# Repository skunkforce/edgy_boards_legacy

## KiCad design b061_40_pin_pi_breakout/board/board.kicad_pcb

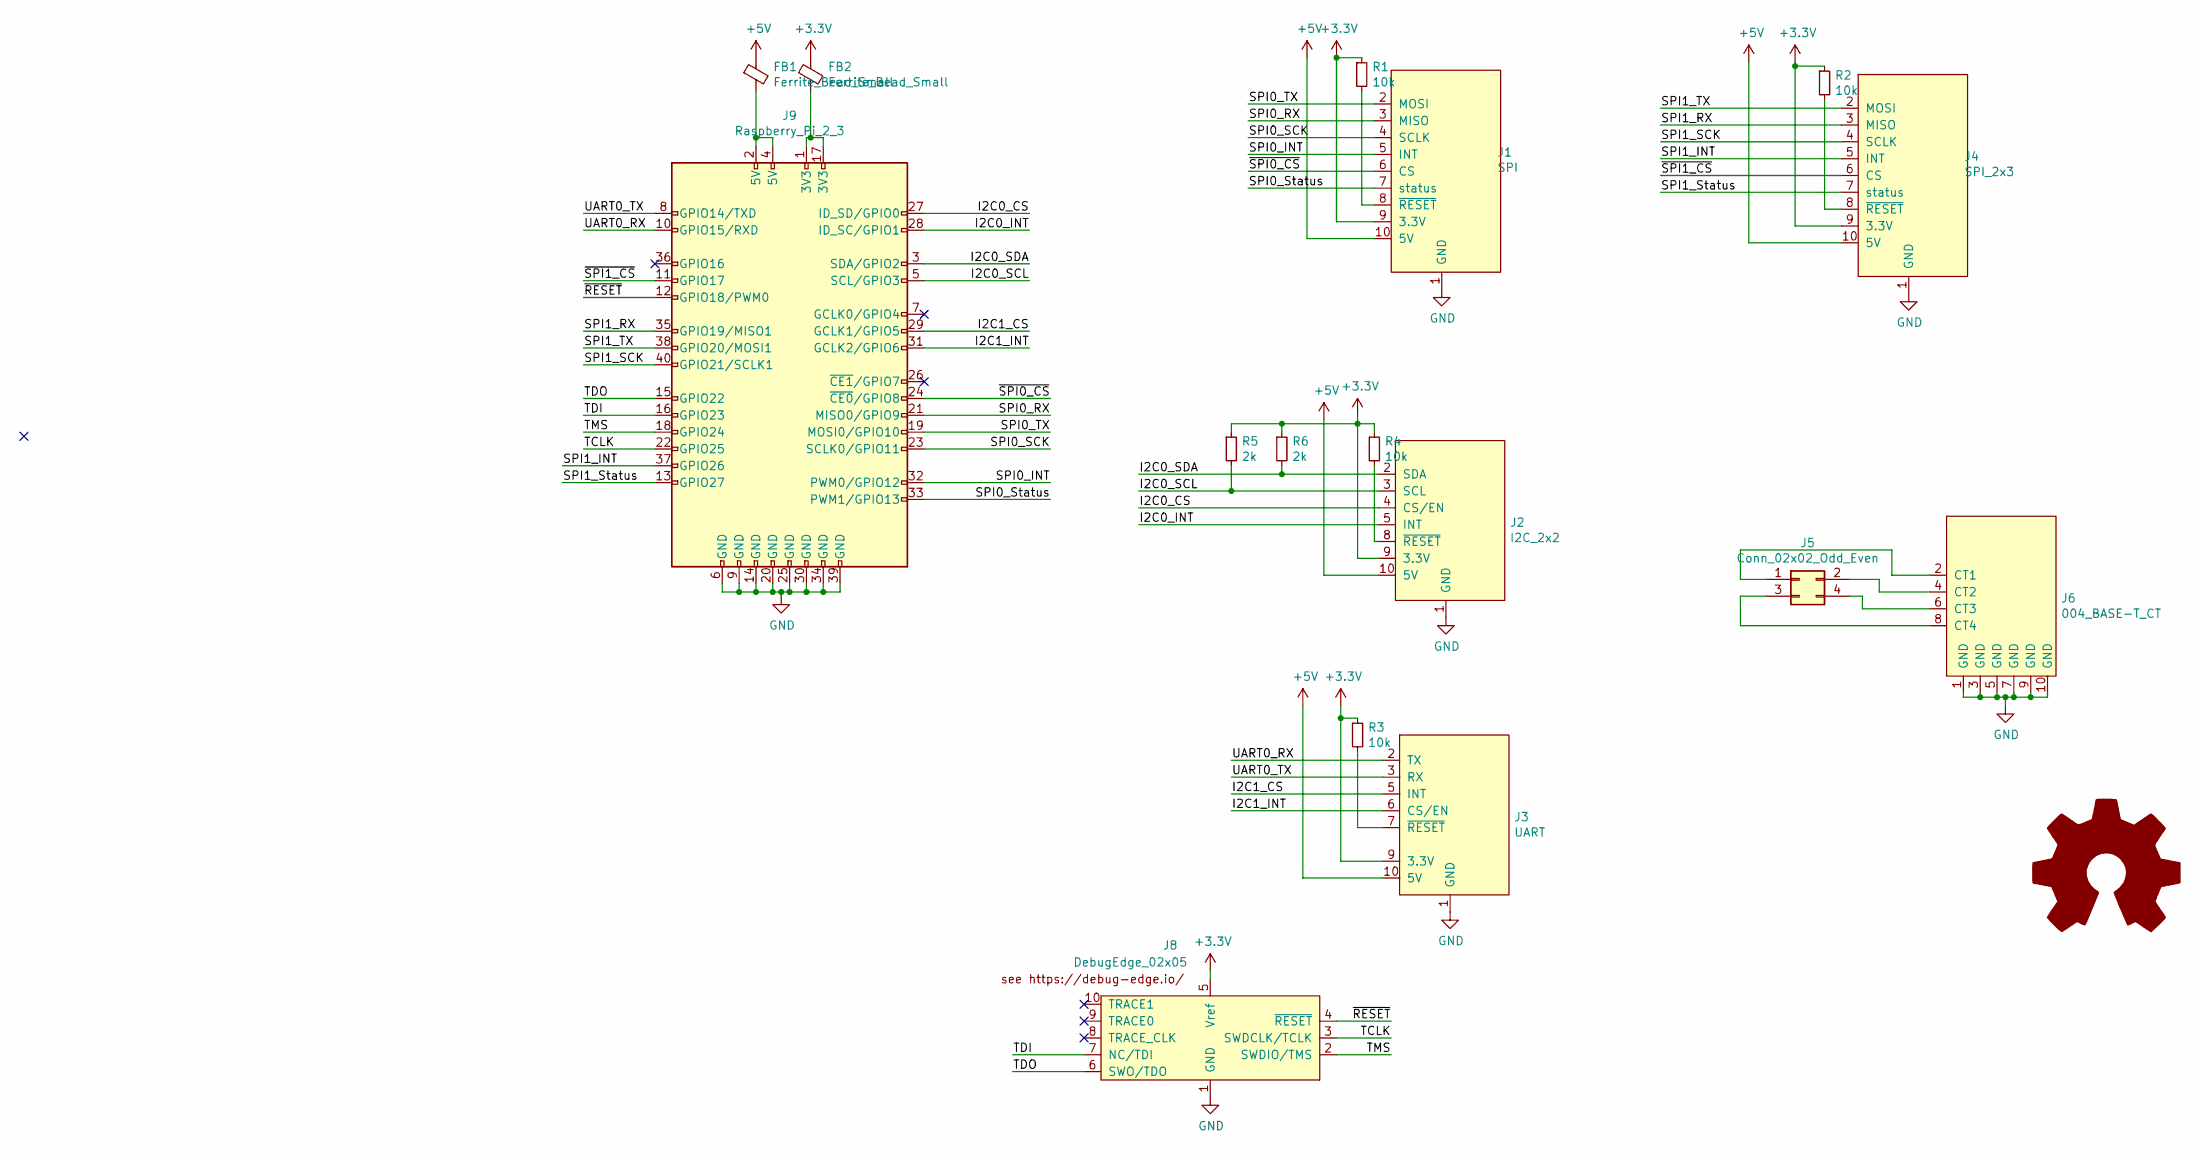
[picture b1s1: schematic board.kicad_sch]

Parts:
FB1, FB2: Ferrite_Bead_Small; L_0805_2012Metric
J1: SPI; on_edge_2x05_up_host
J2: I2C_2x2; on_edge_2x05_host
J3: UART; on_edge_2x05_host
J4: SPI_2x3; on_edge_2x05_host
J5: Conn_02x02_Odd_Even; PinSocket_2x02_P2.54mm_Vertical
J6: 004_BASE-T_CT; on_edge_2x05_up_host
J8: DebugEdge_02x05; debug_edge_2x05_host
J9: Raspberry_Pi_2_3; PinSocket_2x20_P2.54mm_Vertical
R1, R2, R3, R4: 10k; R_0603_1608Metric
R5, R6: 2k; R_0603_1608Metric
l1: Logo_Open_Hardware_Large; OSHW-Logo2_7.3x6mm_SilkScreen

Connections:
+3V3: FB2.1, J1.9 (3.3V), J2.9 (3.3V), J3.9 (3.3V), J4.9 (3.3V), J8.5 (Vref), R1.1, R2.1, R3.1, R4.1, R5.1, R6.1
+5V: FB1.1, J1.10 (5V), J2.10 (5V), J3.10 (5V), J4.10 (5V)
/I2C0_CS: J2.4 (CS/EN), J9.27 (ID_SD/GPIO0)
/I2C0_INT: J2.5 (INT), J9.28 (ID_SC/GPIO1)
/I2C0_SCL: J2.3 (SCL), J9.5 (SCL/GPIO3), R5.2
/I2C0_SDA: J2.2 (SDA), J9.3 (SDA/GPIO2), R6.2
/I2C1_CS: J3.5 (INT), J9.29 (GCLK1/GPIO5)
/I2C1_INT: J3.6 (CS/EN), J9.31 (GCLK2/GPIO6)
/SPI0_INT: J1.5 (INT), J9.32 (PWM0/GPIO12)
/SPI0_RX: J1.3 (MISO), J9.21 (MISO0/GPIO9)
/SPI0_SCK: J1.4 (SCLK), J9.23 (SCLK0/GPIO11)
/SPI0_Status: J1.7 (status), J9.33 (PWM1/GPIO13)
/SPI0_TX: J1.2 (MOSI), J9.19 (MOSI0/GPIO10)
/SPI1_INT: J4.5 (INT), J9.37 (GPIO26)
/SPI1_RX: J4.3 (MISO), J9.35 (GPIO19/MISO1)
/SPI1_SCK: J4.4 (SCLK), J9.40 (GPIO21/SCLK1)
/SPI1_Status: J4.7 (status), J9.13 (GPIO27)
/SPI1_TX: J4.2 (MOSI), J9.38 (GPIO20/MOSI1)
/TCLK: J8.3 (SWDCLK/TCLK), J9.22 (GPIO25)
/TDI: J8.7 (NC/TDI), J9.16 (GPIO23)
/TDO: J8.6 (SWO/TDO), J9.15 (GPIO22)
/TMS: J8.2 (SWDIO/TMS), J9.18 (GPIO24)
/UART0_RX: J3.2 (TX), J9.10 (GPIO15/RXD)
/UART0_TX: J3.3 (RX), J9.8 (GPIO14/TXD)
/~RESET: J8.4 (~RESET), J9.12 (GPIO18/PWM0)
/~SPI0_CS: J1.6 (CS), J9.24 (~CE0/GPIO8)
/~SPI1_CS: J4.6 (CS), J9.11 (GPIO17)
GND: J1.1 (GND), J2.1 (GND), J3.1 (GND), J4.1 (GND), J6.1 (GND), J6.3 (GND), J6.5 (GND), J6.7 (GND), J6.9 (GND), J6.10 (GND), J8.1 (GND), J9.6 (GND), J9.9 (GND), J9.14 (GND), J9.20 (GND), J9.25 (GND), J9.30 (GND), J9.34 (GND), J9.39 (GND)
unnamed: FB1.2, J9.2 (5V), J9.4 (5V)
unnamed: FB2.2, J9.1 (3V3), J9.17 (3V3)
unnamed: J1.8 (~RESET), R1.2
unnamed: J2.8 (~RESET), R4.2
unnamed: J3.7 (~RESET), R3.2
unnamed: J4.8 (~RESET), R2.2
unnamed: J5.1, J6.2 (CT1)
unnamed: J5.2, J6.4 (CT2)
unnamed: J5.3, J6.8 (CT4)
unnamed: J5.4, J6.6 (CT3)

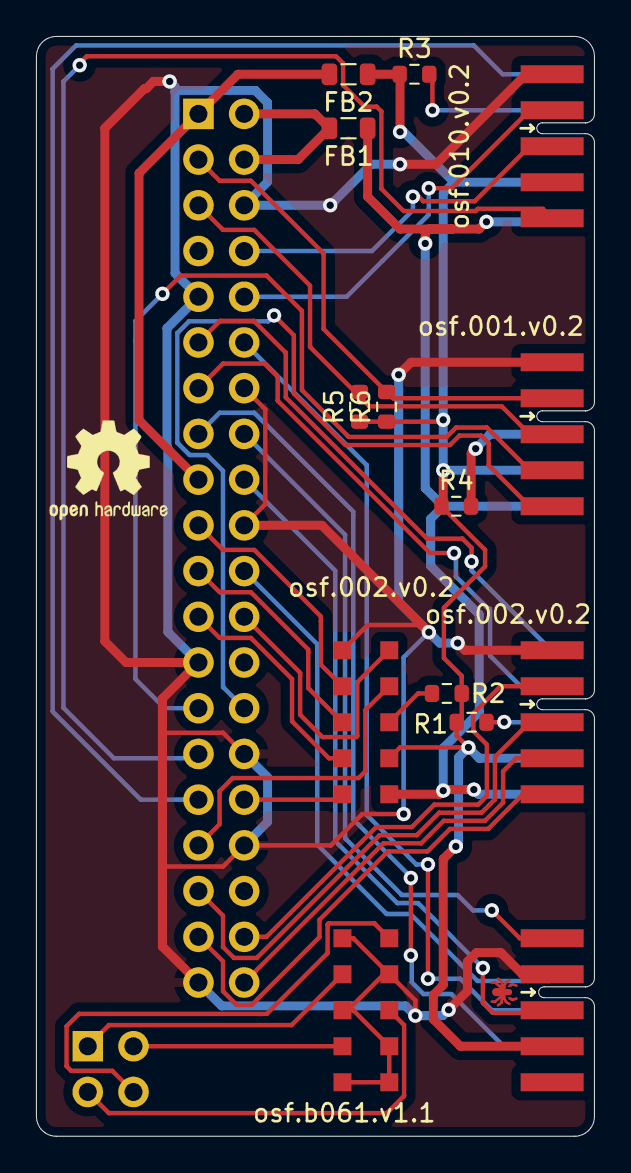
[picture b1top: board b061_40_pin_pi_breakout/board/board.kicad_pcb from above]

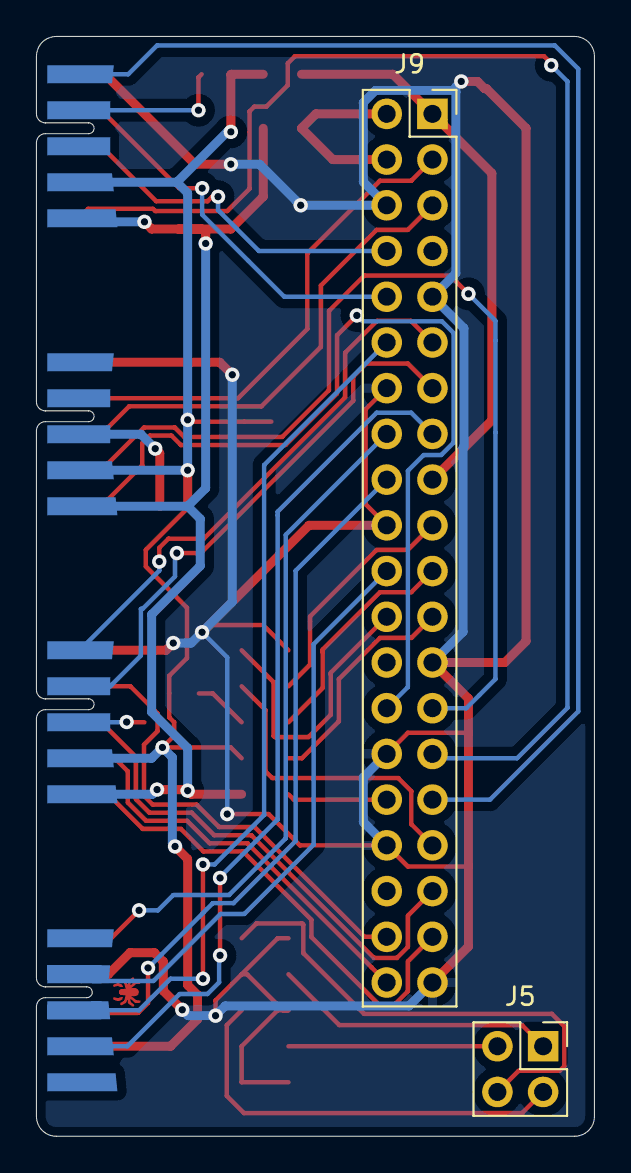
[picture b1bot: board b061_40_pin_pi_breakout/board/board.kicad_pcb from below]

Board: 2 copper layers, 31.0 x 61.1 mm, 17 parts (2 on the bottom side), 38 nets.

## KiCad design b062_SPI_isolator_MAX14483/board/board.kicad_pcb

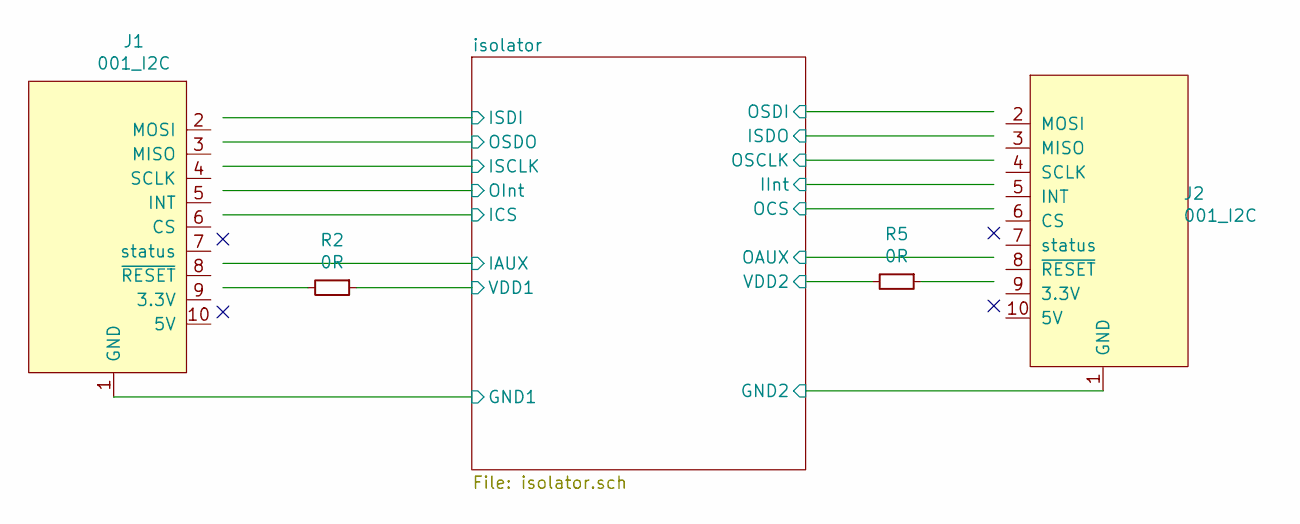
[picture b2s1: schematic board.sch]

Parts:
J1: 001_I2C; on_edge_2x05_device
J2: 001_I2C; on_edge_2x05_host
R2, R5: 0R; R_0603_1608Metric

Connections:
/isolator/GND1: J1.1 (GND); also elsewhere on the board
/isolator/GND2: J2.1 (GND); also elsewhere on the board
/isolator/IAUX: J1.8 (~RESET); also elsewhere on the board
/isolator/ICS: J1.6 (CS); also elsewhere on the board
/isolator/IInt: J2.5 (INT); also elsewhere on the board
/isolator/ISCLK: J1.4 (SCLK); also elsewhere on the board
/isolator/ISDI: J1.2 (MOSI); also elsewhere on the board
/isolator/ISDO: J2.3 (MISO); also elsewhere on the board
/isolator/OAUX: J2.8 (~RESET); also elsewhere on the board
/isolator/OCS: J2.6 (CS); also elsewhere on the board
/isolator/OInt: J1.5 (INT); also elsewhere on the board
/isolator/OSCLK: J2.4 (SCLK); also elsewhere on the board
/isolator/OSDI: J2.2 (MOSI); also elsewhere on the board
/isolator/OSDO: J1.3 (MISO); also elsewhere on the board
/isolator/VDD1: R2.1; also elsewhere on the board
/isolator/VDD2: R5.2; also elsewhere on the board
unnamed: J1.9 (3.3V), R2.2
unnamed: J2.9 (3.3V), R5.1

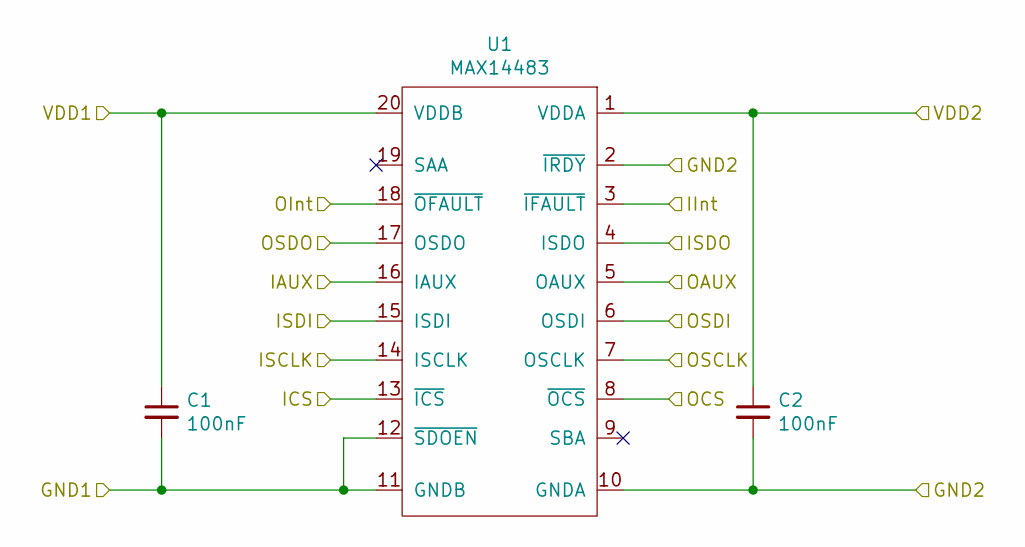
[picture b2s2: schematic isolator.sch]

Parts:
C1, C2: 100nF; C_0603_1608Metric
U1: MAX14483; SSOP-20_5.3x7.2mm_P0.65mm

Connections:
/isolator/GND1: C1.2, U1.11 (GNDB), U1.12 (~SDOEN); also elsewhere on the board
/isolator/GND2: C2.2, U1.2 (~IRDY), U1.10 (GNDA); also elsewhere on the board
/isolator/IAUX: U1.16 (IAUX); also elsewhere on the board
/isolator/ICS: U1.13 (~ICS); also elsewhere on the board
/isolator/IInt: U1.3 (~IFAULT); also elsewhere on the board
/isolator/ISCLK: U1.14 (ISCLK); also elsewhere on the board
/isolator/ISDI: U1.15 (ISDI); also elsewhere on the board
/isolator/ISDO: U1.4 (ISDO); also elsewhere on the board
/isolator/OAUX: U1.5 (OAUX); also elsewhere on the board
/isolator/OCS: U1.8 (~OCS); also elsewhere on the board
/isolator/OInt: U1.18 (~OFAULT); also elsewhere on the board
/isolator/OSCLK: U1.7 (OSCLK); also elsewhere on the board
/isolator/OSDI: U1.6 (OSDI); also elsewhere on the board
/isolator/OSDO: U1.17 (OSDO); also elsewhere on the board
/isolator/VDD1: C1.1, U1.20 (VDDB); also elsewhere on the board
/isolator/VDD2: C2.1, U1.1 (VDDA); also elsewhere on the board

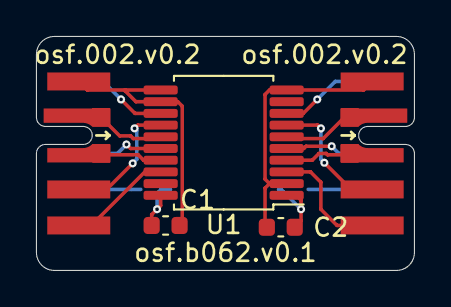
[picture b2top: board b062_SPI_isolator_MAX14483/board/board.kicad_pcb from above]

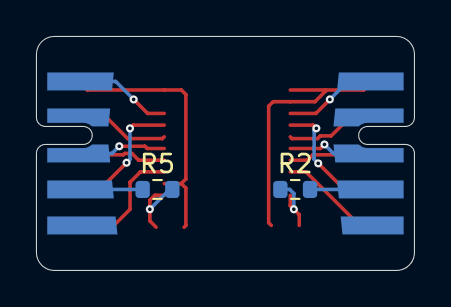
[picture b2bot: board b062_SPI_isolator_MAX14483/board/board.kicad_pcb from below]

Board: 2 copper layers, 21.0 x 13.0 mm, 7 parts (2 on the bottom side), 18 nets.

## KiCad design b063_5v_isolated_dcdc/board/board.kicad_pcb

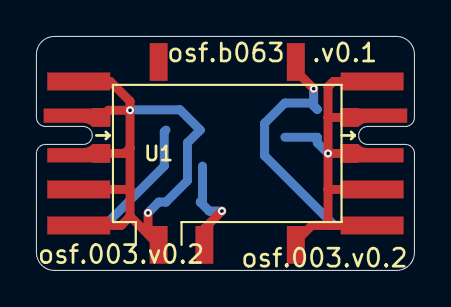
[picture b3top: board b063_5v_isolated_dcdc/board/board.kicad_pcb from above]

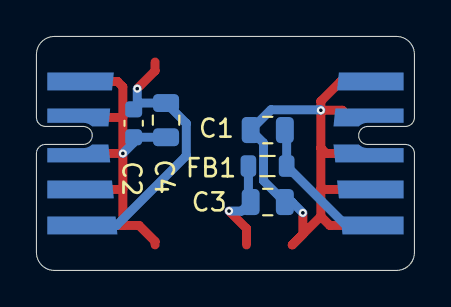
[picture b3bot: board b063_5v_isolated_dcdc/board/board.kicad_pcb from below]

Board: 2 copper layers, 21.0 x 13.0 mm, 8 parts (5 on the bottom side), 5 nets.

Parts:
C1, C3, C4: 10uF; C_0805_2012Metric
C2: 100nF; C_0603_1608Metric
FB1: 0R; L_0805_2012Metric
J1: 003_power; on_edge_2x05_device
J2: 003_power; on_edge_2x05_host
U1: PDS2-S5

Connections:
/isolator/GND1: C1.2, C3.2, J1.1, J1.2, J1.3, J1.4, J1.5, U1.1
/isolator/GND2: C2.2, C4.2, J2.1, J2.2, J2.3, J2.4, J2.5, U1.4
/isolator/VDD1: C1.1, FB1.2, J1.10
/isolator/VDD2: C2.1, C4.1, J2.10, U1.5
unnamed: C3.1, FB1.1, U1.2

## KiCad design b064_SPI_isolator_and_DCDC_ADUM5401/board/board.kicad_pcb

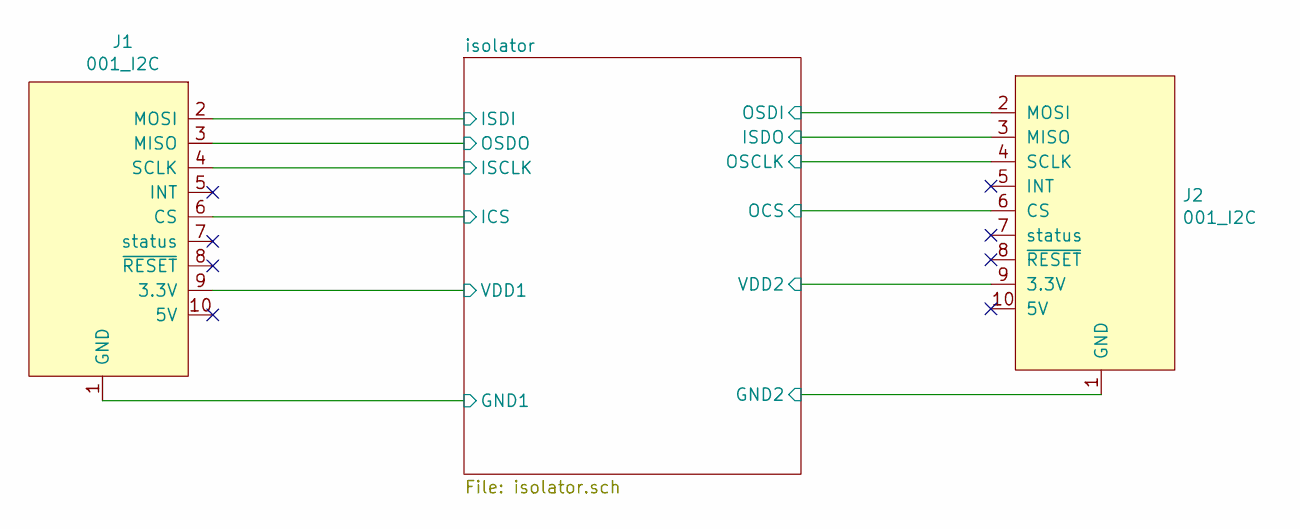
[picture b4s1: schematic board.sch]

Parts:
J1: 001_I2C; on_edge_2x05_device
J2: 001_I2C; on_edge_2x05_host

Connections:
/isolator/GND1: J1.1 (GND); also elsewhere on the board
/isolator/GND2: J2.1 (GND); also elsewhere on the board
/isolator/ICS: J1.6 (CS); also elsewhere on the board
/isolator/ISCLK: J1.4 (SCLK); also elsewhere on the board
/isolator/ISDI: J1.2 (MOSI); also elsewhere on the board
/isolator/ISDO: J2.3 (MISO); also elsewhere on the board
/isolator/OCS: J2.6 (CS); also elsewhere on the board
/isolator/OSCLK: J2.4 (SCLK); also elsewhere on the board
/isolator/OSDI: J2.2 (MOSI); also elsewhere on the board
/isolator/OSDO: J1.3 (MISO); also elsewhere on the board
/isolator/VDD1: J1.9 (3.3V); also elsewhere on the board
/isolator/VDD2: J2.9 (3.3V); also elsewhere on the board

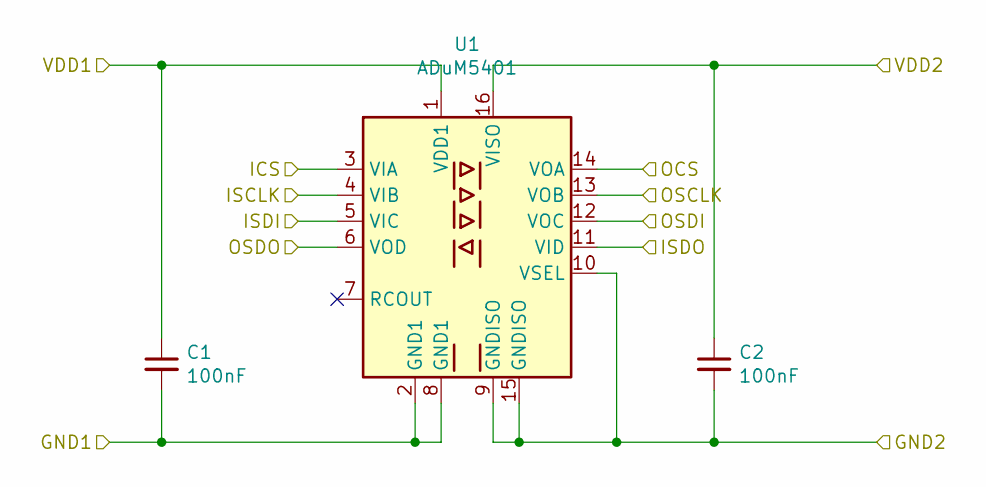
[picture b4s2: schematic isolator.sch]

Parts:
C1, C2: 100nF; C_0603_1608Metric
U1: ADuM5401; SOIC-16W_7.5x10.3mm_P1.27mm

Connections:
/isolator/GND1: C1.2, U1.2 (GND1), U1.8 (GND1); also elsewhere on the board
/isolator/GND2: C2.2, U1.9 (GNDISO), U1.10 (VSEL), U1.15 (GNDISO); also elsewhere on the board
/isolator/ICS: U1.3 (VIA); also elsewhere on the board
/isolator/ISCLK: U1.4 (VIB); also elsewhere on the board
/isolator/ISDI: U1.5 (VIC); also elsewhere on the board
/isolator/ISDO: U1.11 (VID); also elsewhere on the board
/isolator/OCS: U1.14 (VOA); also elsewhere on the board
/isolator/OSCLK: U1.13 (VOB); also elsewhere on the board
/isolator/OSDI: U1.12 (VOC); also elsewhere on the board
/isolator/OSDO: U1.6 (VOD); also elsewhere on the board
/isolator/VDD1: C1.1, U1.1 (VDD1); also elsewhere on the board
/isolator/VDD2: C2.1, U1.16 (VISO); also elsewhere on the board

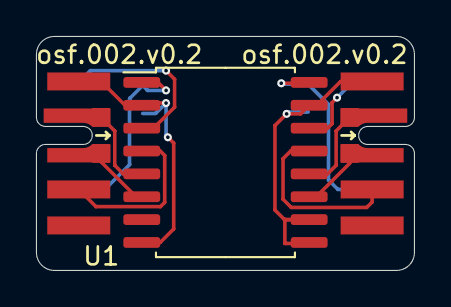
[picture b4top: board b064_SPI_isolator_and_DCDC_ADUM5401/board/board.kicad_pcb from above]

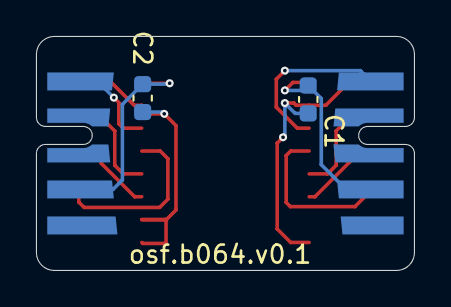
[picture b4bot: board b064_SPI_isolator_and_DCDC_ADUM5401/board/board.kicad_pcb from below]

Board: 2 copper layers, 21.0 x 13.0 mm, 5 parts (2 on the bottom side), 12 nets.

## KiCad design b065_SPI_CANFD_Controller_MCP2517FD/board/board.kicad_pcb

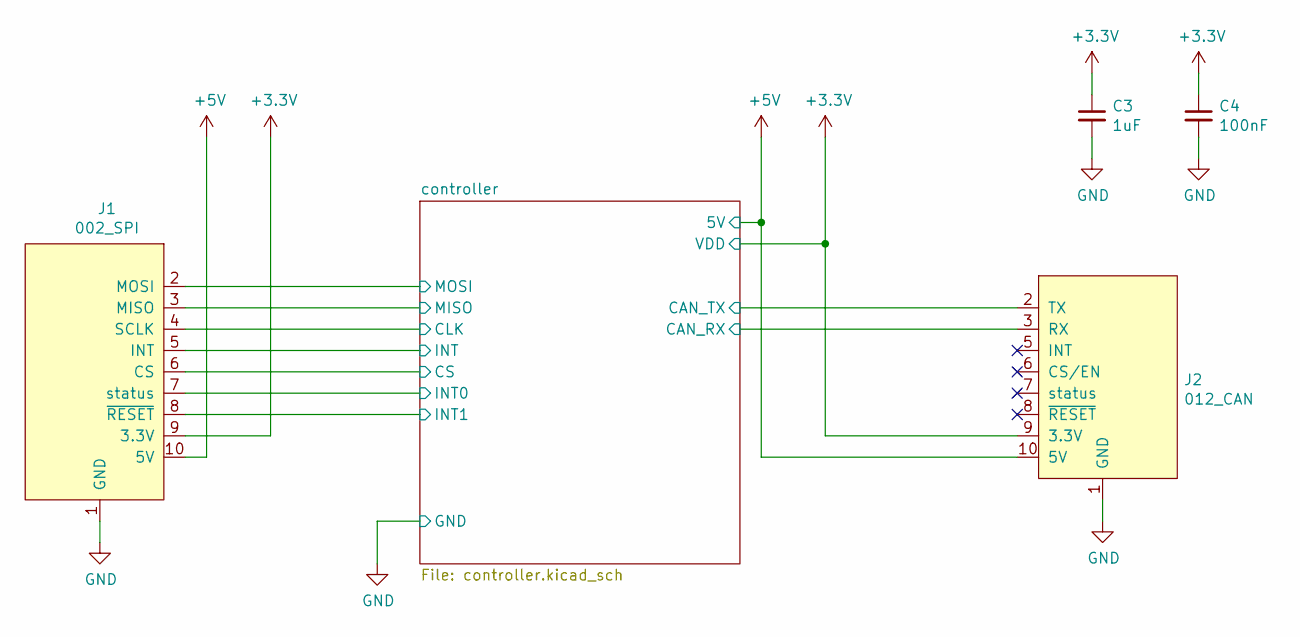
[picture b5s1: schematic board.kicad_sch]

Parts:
C3: 1uF; C_0603_1608Metric; Voltage 6.3V
C4: 100nF; C_0603_1608Metric; Voltage 6.3V
J1: 002_SPI; on_edge_2x05_device
J2: 012_CAN; on_edge_2x05_host

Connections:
+3V3: C3.1, C4.1, J1.9 (3.3V), J2.9 (3.3V); also elsewhere on the board
+5V: J1.10 (5V), J2.10 (5V)
/controller/CAN_RX: J2.3 (RX); also elsewhere on the board
/controller/CAN_TX: J2.2 (TX); also elsewhere on the board
/controller/CLK: J1.4 (SCLK); also elsewhere on the board
/controller/CS: J1.6 (CS); also elsewhere on the board
/controller/INT: J1.5 (INT); also elsewhere on the board
/controller/INT0: J1.7 (status); also elsewhere on the board
/controller/INT1: J1.8 (~RESET); also elsewhere on the board
/controller/MISO: J1.3 (MISO); also elsewhere on the board
/controller/MOSI: J1.2 (MOSI); also elsewhere on the board
GND: C3.2, C4.2, J1.1 (GND), J2.1 (GND); also elsewhere on the board

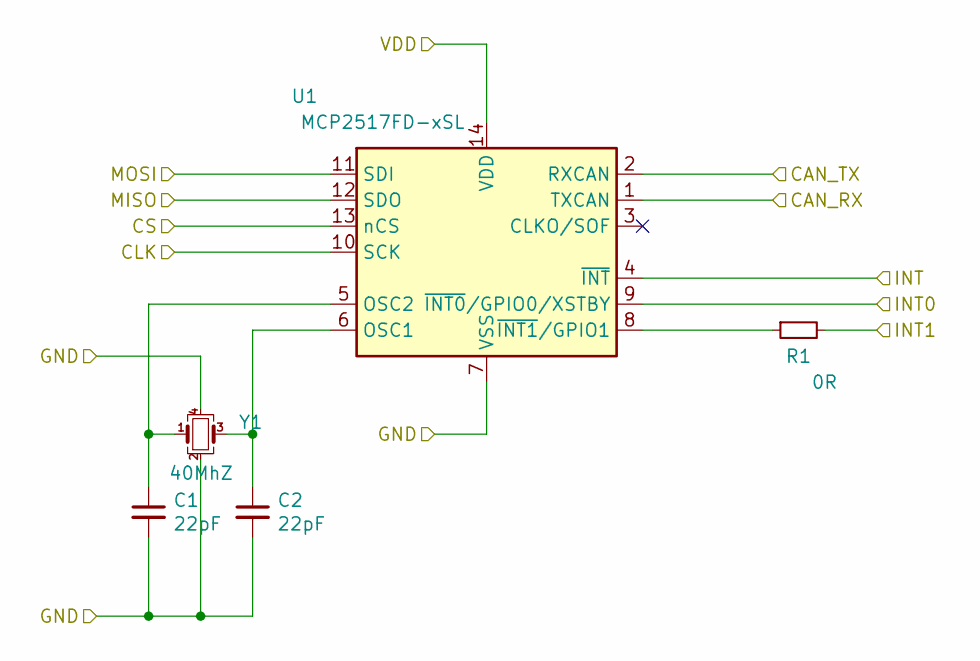
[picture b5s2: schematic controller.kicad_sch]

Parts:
C1, C2: 22pF; C_0603_1608Metric; Voltage 6.3V
R1: 0R; R_0603_1608Metric
U1: MCP2517FD-xSL; SOIC-14_3.9x8.7mm_P1.27mm; MPN MCP2517FD-H/SL
Y1: 40MhZ; Crystal_SMD_Abracon_ABM8G-4Pin_3.2x2.5mm; MPN RH100-40.000-18-F-2050-TR

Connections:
+3V3: U1.14 (VDD); also elsewhere on the board
/controller/CAN_RX: U1.1 (TXCAN); also elsewhere on the board
/controller/CAN_TX: U1.2 (RXCAN); also elsewhere on the board
/controller/CLK: U1.10 (SCK); also elsewhere on the board
/controller/CS: U1.13 (nCS); also elsewhere on the board
/controller/INT: U1.4 (~INT); also elsewhere on the board
/controller/INT0: U1.9 (~INT0/GPIO0/XSTBY); also elsewhere on the board
/controller/INT1: R1.2; also elsewhere on the board
/controller/MISO: U1.12 (SDO); also elsewhere on the board
/controller/MOSI: U1.11 (SDI); also elsewhere on the board
GND: C1.2, C2.2, U1.7 (VSS), Y1.2, Y1.4; also elsewhere on the board
unnamed: C1.1, U1.5 (OSC2), Y1.1
unnamed: C2.1, U1.6 (OSC1), Y1.3
unnamed: R1.1, U1.8 (~INT1/GPIO1)

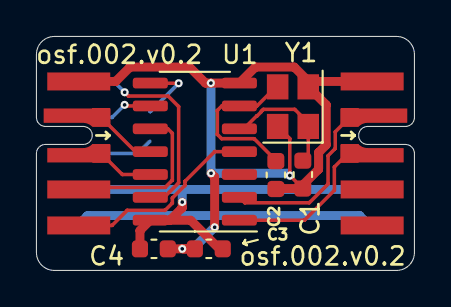
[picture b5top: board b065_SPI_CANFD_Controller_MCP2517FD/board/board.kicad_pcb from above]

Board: 2 copper layers, 21.0 x 13.0 mm, 9 parts (1 on the bottom side), 15 nets.

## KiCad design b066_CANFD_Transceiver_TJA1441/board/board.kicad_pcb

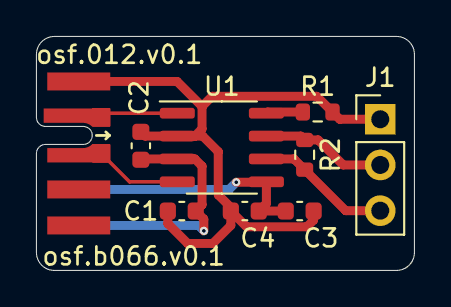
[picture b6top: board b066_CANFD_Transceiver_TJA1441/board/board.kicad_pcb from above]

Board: 2 copper layers, 21.0 x 13.0 mm, 9 parts (0 on the bottom side), 8 nets.

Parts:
C1, C3: 1uF; C_0603_1608Metric
C2, C4: 100nF; C_0603_1608Metric
J1: Conn_01x03_Male; PinHeader_1x03_P2.54mm_Vertical
J2: 012_CAN; on_edge_2x05_device
R1: 0R; R_0603_1608Metric
R2: NC; R_0603_1608Metric
U1: TJA1441; SOIC-8_3.9x4.9mm_P1.27mm

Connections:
+3V3: C3.1, C4.1, J2.9, U1.5
+5V: C1.1, C2.1, J2.10, U1.3
/controller/CANH: J1.2, R2.1, U1.7
/controller/CANL: J1.3, R2.2, U1.6
/controller/CAN_RX: J2.3, U1.4
/controller/CAN_TX: J2.2, U1.1
GND: C1.2, C2.2, C3.2, C4.2, J1.1, J2.1, R1.2, U1.2
unnamed: R1.1, U1.8

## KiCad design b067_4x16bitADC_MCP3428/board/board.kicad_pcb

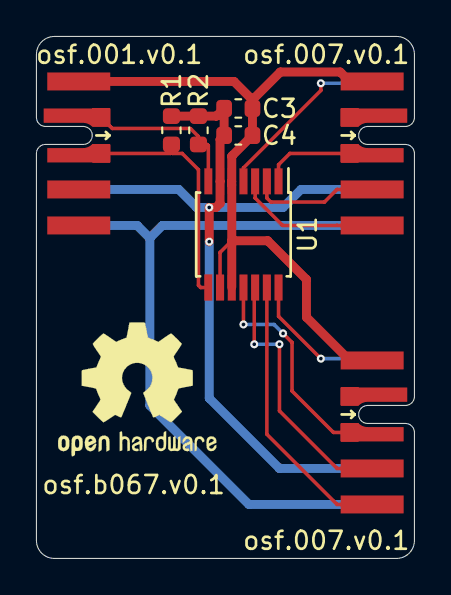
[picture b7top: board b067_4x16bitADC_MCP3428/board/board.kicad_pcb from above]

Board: 2 copper layers, 21.0 x 29.0 mm, 9 parts (0 on the bottom side), 13 nets.

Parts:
C3: 1uF; C_0603_1608Metric
C4: 100nF; C_0603_1608Metric
J1: 001_I2C; on_edge_2x05_device
J2, J3: 007_ADC; on_edge_2x05_host
LOGO1: Logo_Open_Hardware_Small; OSHW-Logo2_9.8x8mm_SilkScreen
R1, R2: 2.2k; R_0603_1608Metric
U1: MCP3428; TSSOP-14_4.4x5mm_P0.65mm

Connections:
+3V3: C3.1, C4.1, J1.9, J2.9, J3.9, R1.1, R2.1, U1.6
+5V: J1.10, J2.10, J3.10
/adc/INH1: J2.3, U1.1
/adc/INH2: J2.5, U1.3
/adc/INH3: J3.3, U1.11
/adc/INH4: J3.5, U1.13
/adc/INL1: J2.4, U1.2
/adc/INL2: J2.6, U1.4
/adc/INL3: J3.4, U1.12
/adc/INL4: J3.6, U1.14
/adc/SCL: J1.3, R1.2, U1.8
/adc/SDA: J1.2, R2.2, U1.7
GND: C3.2, C4.2, J1.1, J2.1, J3.1, U1.5, U1.9, U1.10

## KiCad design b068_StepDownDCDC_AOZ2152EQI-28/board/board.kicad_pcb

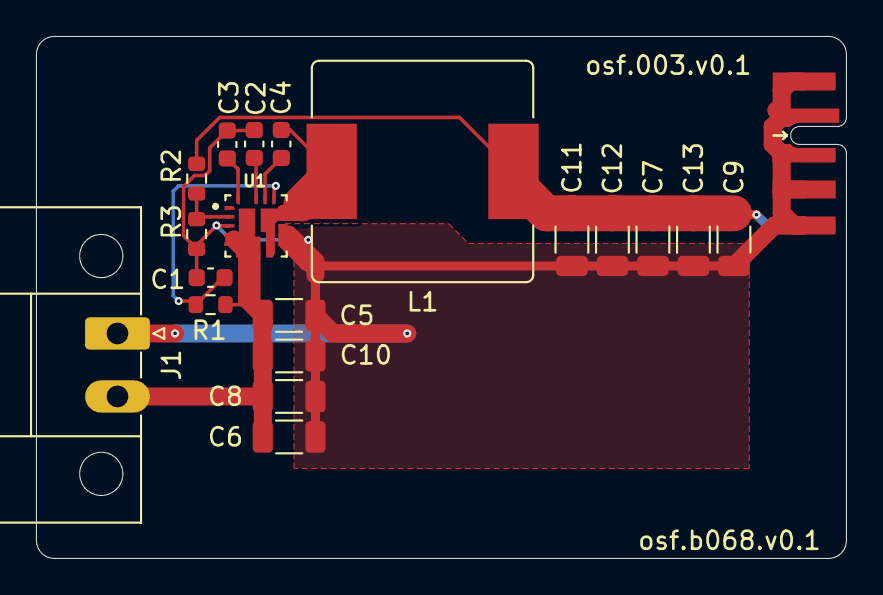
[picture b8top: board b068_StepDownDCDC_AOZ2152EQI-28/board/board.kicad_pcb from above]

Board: 2 copper layers, 45.0 x 29.0 mm, 20 parts (0 on the bottom side), 9 nets.

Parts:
C1: 100pF; C_0603_1608Metric
C2: 4.7uF; C_0603_1608Metric
C3: 10nF; C_0603_1608Metric
C4: 100nF; C_0603_1608Metric
C5, C6, C8, C10: 10uF; R_1206_3216Metric
C7, C9, C11, C12, C13: 22uF; R_1206_3216Metric
J1: Screw_Terminal_01x02; PhoenixContact_MC_1,5_2-GF-3.5_1x02_P3.50mm_Horizontal_Thre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
J2: 003_power; on_edge_2x05_host
L1: 2.2uH; L_Bourns_SRR1210A
R1: 500k; R_0603_1608Metric
R2: 52.3k; R_0603_1608Metric
R3: 10k; R_0603_1608Metric
U1: AOZ2152EQI-28; IC_AOZ2153EQI-30

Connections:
/DCDC/5V: C7.1, C9.1, C11.1, C12.1, C13.1, J2.10, L1.1, R2.1
/DCDC/IN: C5.1, C6.1, C8.1, C10.1, J1.2, R1.1, U1.4, U1.5, U1.6, U1.7, U1.8
GND: C1.2, C2.2, C3.2, C5.2, C6.2, C7.2, C8.2, C9.2, C10.2, C11.2, C12.2, C13.2, J1.1, J2.1, J2.2, J2.3, J2.4, J2.5, R3.2, U1.3, U1.10, U1.11, U1.12
unnamed: C1.1, R1.2, U1.15
unnamed: C2.1, U1.17
unnamed: C3.1, U1.18
unnamed: C4.1, U1.16
unnamed: C4.2, L1.2, U1.9, U1.13, U1.14
unnamed: R2.2, R3.1, U1.2
